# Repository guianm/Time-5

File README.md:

# Time 5
Warthog Robotics - Repositório do time 5 para o projeto da "faquinhas"/projeto se vira nos 30 dias

### Documentos
http://bit.ly/2vsZiPx

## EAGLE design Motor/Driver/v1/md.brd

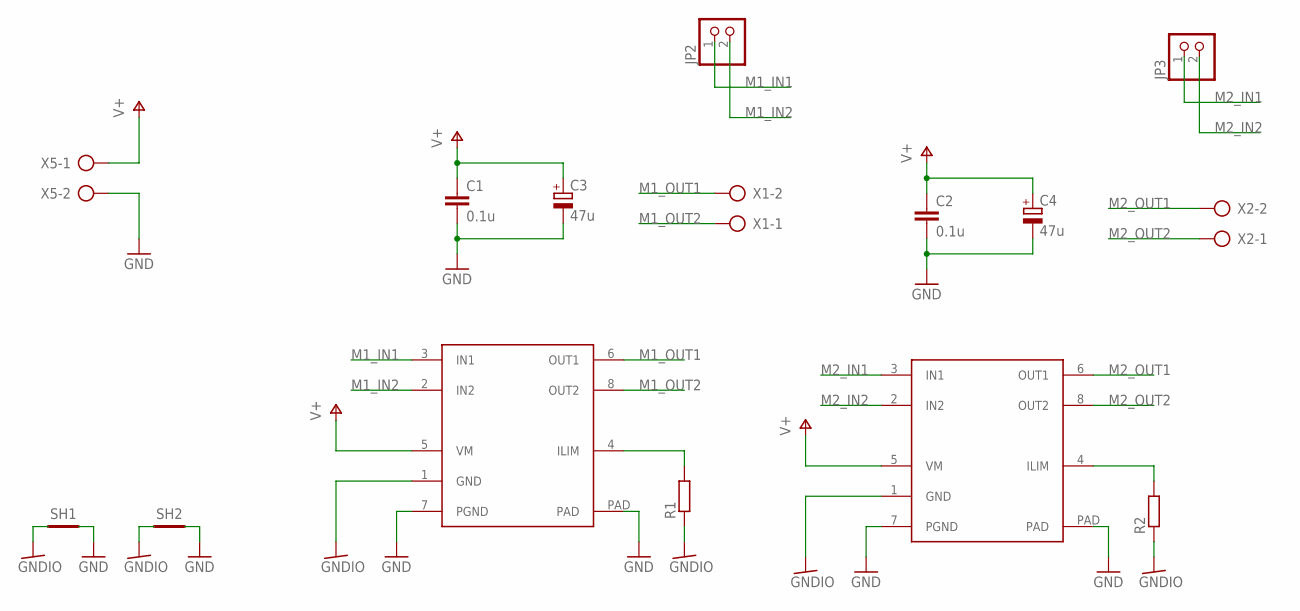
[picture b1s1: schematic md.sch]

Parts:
C1, C2: 0.1u; C0805
C3, C4: 47u; E2,5-7
JP2, JP3: PINHD-1X2; 1X02
MD1, MD2: DRV8871; SO8-COOL
R1, R2: R-EU_0207/7; 0207/7
SH1, SH2: SHORTT5; SHORT_TOP-50
X1, X2, X5: AK300/2

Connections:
GND: C1.2, C2.2, C3.-, C4.-, MD1.7 (PGND), MD1.PAD, MD2.7 (PGND), MD2.PAD, SH1.2, SH2.2, X5.2
GNDIO: MD1.1 (GND), MD2.1 (GND), R1.1, R2.1, SH1.1, SH2.1
M1_IN1: JP2.1, MD1.3 (IN1)
M1_IN2: JP2.2, MD1.2 (IN2)
M1_OUT1: MD1.6 (OUT1), X1.2
M1_OUT2: MD1.8 (OUT2), X1.1
M2_IN1: JP3.1, MD2.3 (IN1)
M2_IN2: JP3.2, MD2.2 (IN2)
M2_OUT1: MD2.6 (OUT1), X2.2
M2_OUT2: MD2.8 (OUT2), X2.1
unnamed: MD1.4 (ILIM), R1.2
unnamed: MD2.4 (ILIM), R2.2
V+: C1.1, C2.1, C3.+, C4.+, MD1.5 (VM), MD2.5 (VM), X5.1

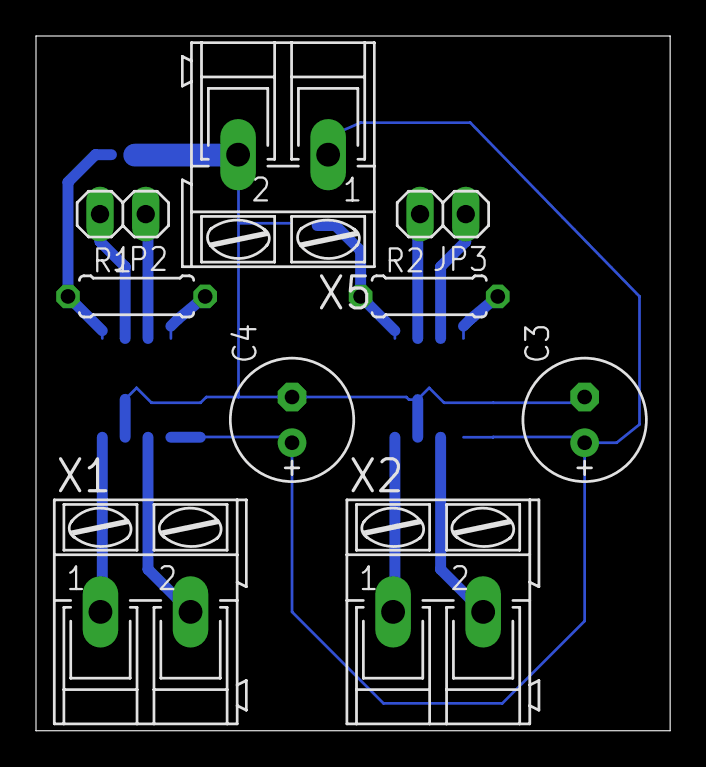
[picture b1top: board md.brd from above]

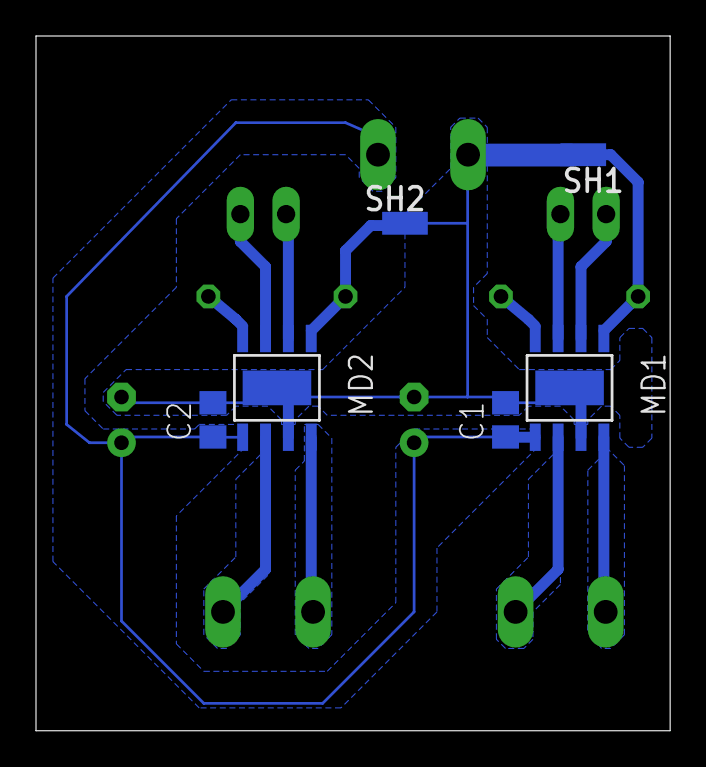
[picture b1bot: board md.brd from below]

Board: 2 copper layers, 35.2 x 38.6 mm, 15 parts (6 on the bottom side), 13 nets.

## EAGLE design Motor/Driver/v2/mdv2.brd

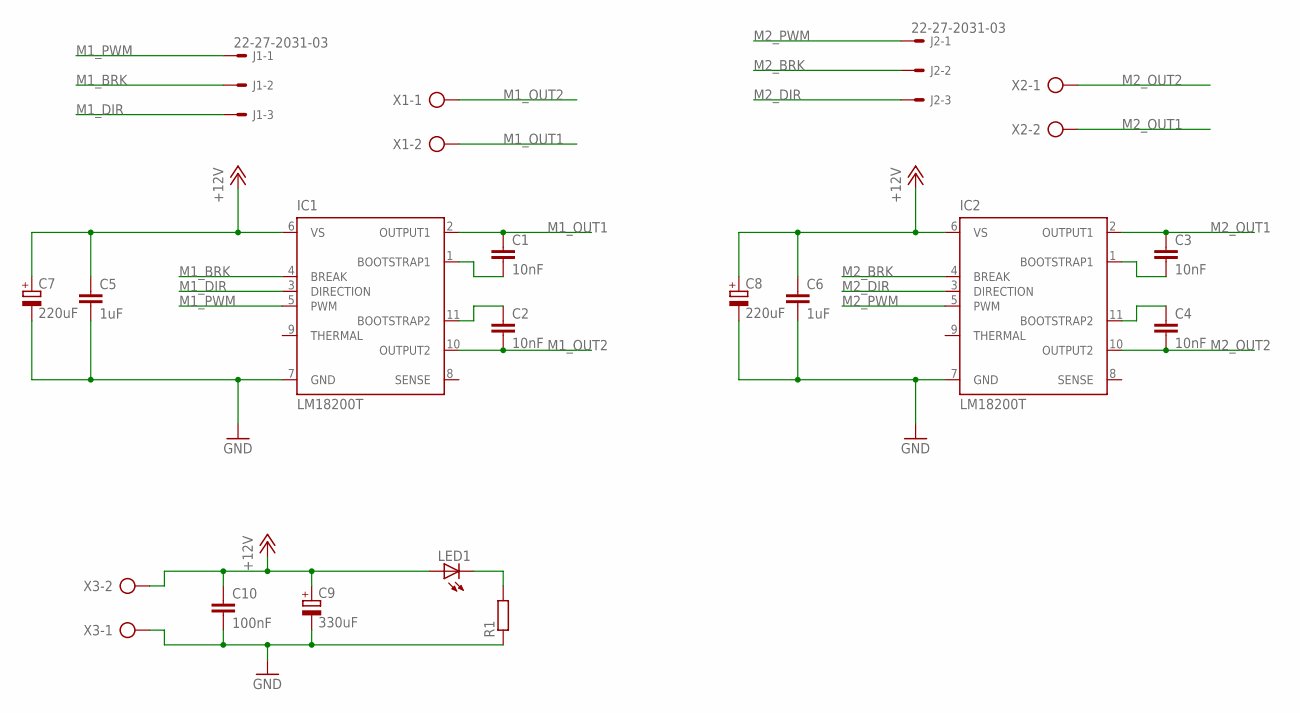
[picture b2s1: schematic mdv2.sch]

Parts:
C1, C2, C3, C4: 10nF; C050-025X075
C5, C6: 1uF; C050-045X075
C7, C8: 220uF; E3,5-8
C9: 330uF; E3,5-8
C10: 100nF; C050-025X075
IC1, IC2: LM18200T; TO-220-11
J1, J2: 22-27-2031-03; 6410-03
LED1: LED5MM
R1: R-EU_0207/7; 0207/7
X1, X2, X3: AK300/2

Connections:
+12V: C5.1, C6.1, C7.+, C8.+, C9.+, C10.1, IC1.6 (VS), IC2.6 (VS), LED1.A, X3.2
GND: C5.2, C6.2, C7.-, C8.-, C9.-, C10.2, IC1.7 (GND), IC2.7 (GND), R1.1, X3.1
M1_BRK: IC1.4 (BREAK), J1.2
M1_DIR: IC1.3 (DIRECTION), J1.3
M1_OUT1: C1.1, IC1.2 (OUTPUT1), X1.2
M1_OUT2: C2.2, IC1.10 (OUTPUT2), X1.1
M1_PWM: IC1.5 (PWM), J1.1
M2_BRK: IC2.4 (BREAK), J2.2
M2_DIR: IC2.3 (DIRECTION), J2.3
M2_OUT1: C3.1, IC2.2 (OUTPUT1), X2.2
M2_OUT2: C4.2, IC2.10 (OUTPUT2), X2.1
M2_PWM: IC2.5 (PWM), J2.1
unnamed: LED1.K (C), R1.2
unnamed: C1.2, IC1.1 (BOOTSTRAP1)
unnamed: C2.1, IC1.11 (BOOTSTRAP2)
unnamed: C3.2, IC2.1 (BOOTSTRAP1)
unnamed: C4.1, IC2.11 (BOOTSTRAP2)

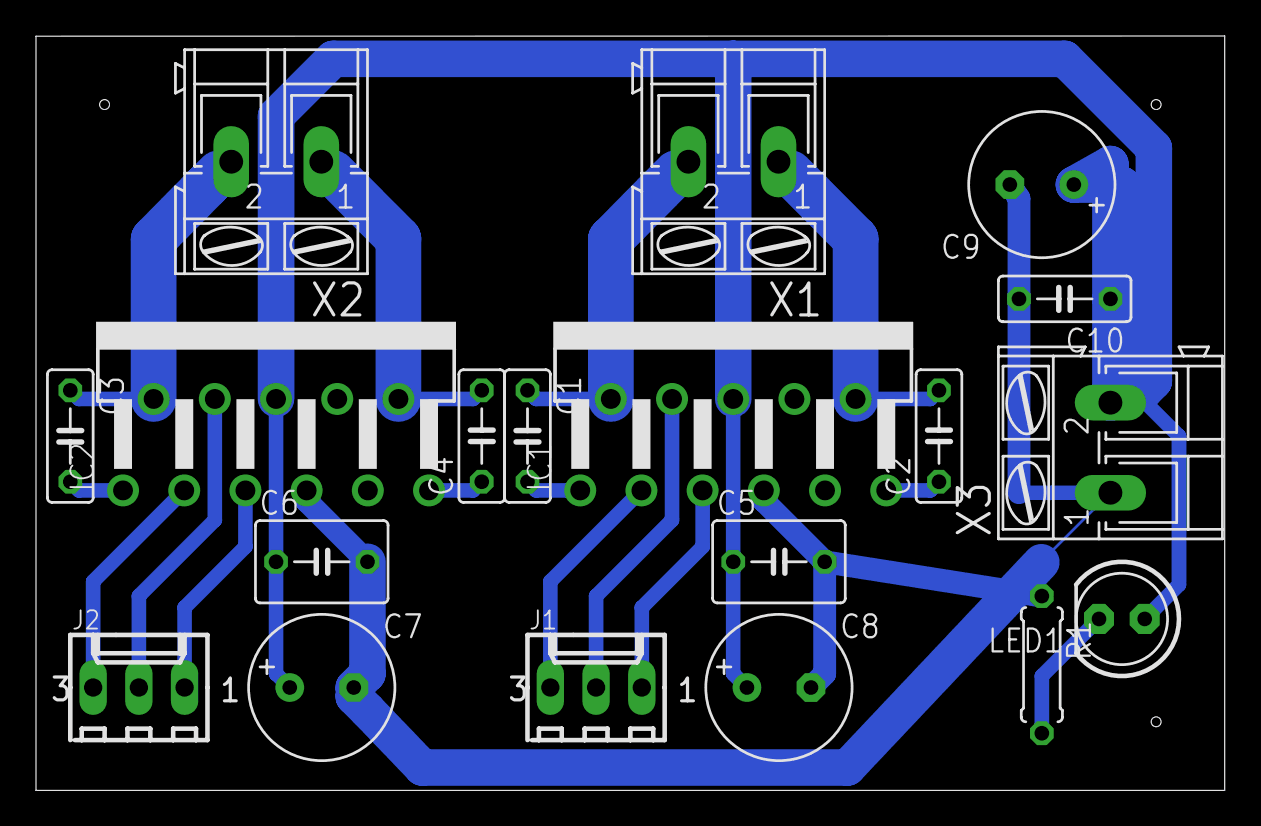
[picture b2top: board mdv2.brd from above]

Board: 2 copper layers, 66.0 x 41.9 mm, 19 parts (0 on the bottom side), 17 nets.

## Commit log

2017-08-24 Updates README.
2017-08-31 Adding the Power Board informations
2017-09-01 Finishing ideas for regulator. It's a better idea to use a switching regulator what's efficience is higher, or even a power bank
2017-09-01 Blabalabal
2017-09-02 Adds motor driver files.
2017-09-11 Adds Hokuyo laser documents.
2017-09-12 Adds architecture diagram files.
2017-09-12 Adds missing documents from initial planning (needs organization)
2017-09-13 Adds missing files.
2017-09-21 Adding mechanicals design!
2017-09-21 Adds bucha gcode file.
2017-09-22 Mechanical Design changes
2017-09-22 Master reorganization
2017-09-22 Last commit for lluchiari on mechanics
2017-09-22 Add main vision code and a PiCamera working prototype
2017-09-22 Change visual tracking to perform detection using visual moment
2017-09-23 Correct the red color threshold and add output of targets for the AI
2017-09-23 Add AI state machine and GPIO control
